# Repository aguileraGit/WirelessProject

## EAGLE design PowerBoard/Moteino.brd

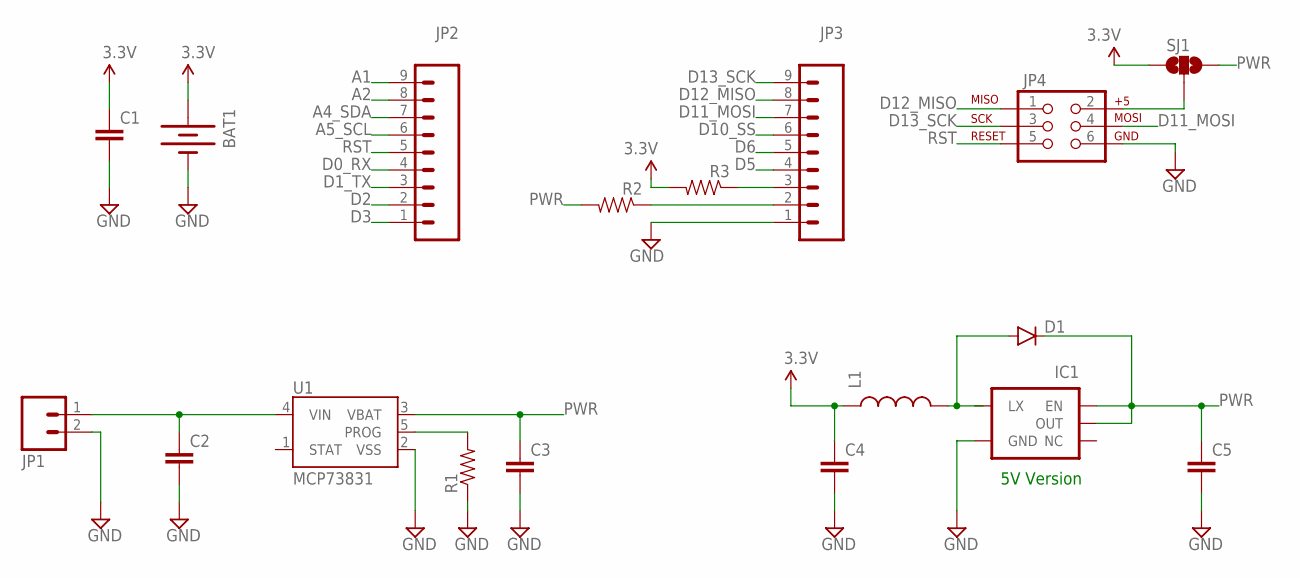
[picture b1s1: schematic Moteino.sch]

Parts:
BAT1: BATTERY12MM; BATTCON_12MM
C1, C2, C3, C4, C5: CAP0603-CAP; 0603-CAP
D1: DIODESMA; SMA-DIODE
IC1: V_REG_NCP1400SOT23-5; SOT23-5
JP1: M02PTH; 1X02
JP2, JP3: M09; 1X09
JP4: AVR_SPI_PRG_6TESTPOINTS; 2X3_TEST_POINTS
L1: INDUCTORINDUCTOR_4.7UH; INDUCTOR_4.7UH
R1, R2, R3: RESISTOR0603-RES; 0603-RES
SJ1: JUMPER-PAD-3-NOFULL_BOX_SILK; PAD-JUMPER-3-NO_YES_SILK_FULL_BOX
U1: MCP73831; SOT23-5

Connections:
A1: JP2.9
A2: JP2.8
A4_SDA: JP2.7
A5_SCL: JP2.6
D0_RX: JP2.4
D1_TX: JP2.3
D2: JP2.2
D3: JP2.1
D5: JP3.4
D6: JP3.5
D10_SS: JP3.6
D11_MOSI: JP3.7, JP4.4
D12_MISO: JP3.8, JP4.1
D13_SCK: JP3.9, JP4.3
GND: BAT1.GND (-), C1.2, C2.2, C3.2, C4.2, C5.2, IC1.4 (GND), JP1.2, JP3.1, JP4.6, R1.1, U1.2 (VSS)
unnamed: JP3.2, R2.1
unnamed: JP3.3, R3.1
unnamed: C2.1, JP1.1, U1.4 (VIN)
unnamed: R1.2, U1.5 (PROG)
unnamed: D1.A, L1.P$2 (2)
unnamed: JP4.2, SJ1.2
PWR: C3.1, C5.1, D1.C, IC1.1 (EN), IC1.2 (OUT), R2.2, SJ1.3, U1.3 (VBAT)
RST: JP2.5, JP4.5
VCC: BAT1.PWR@1 (+), C1.1, C4.1, L1.P$1 (1), R3.2, SJ1.1

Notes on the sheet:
5V Version

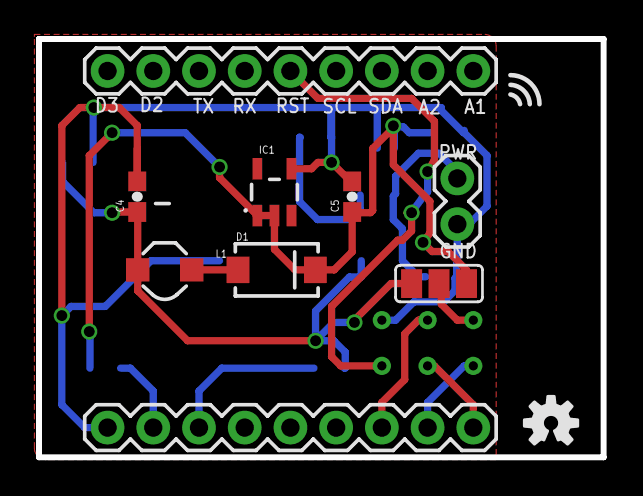
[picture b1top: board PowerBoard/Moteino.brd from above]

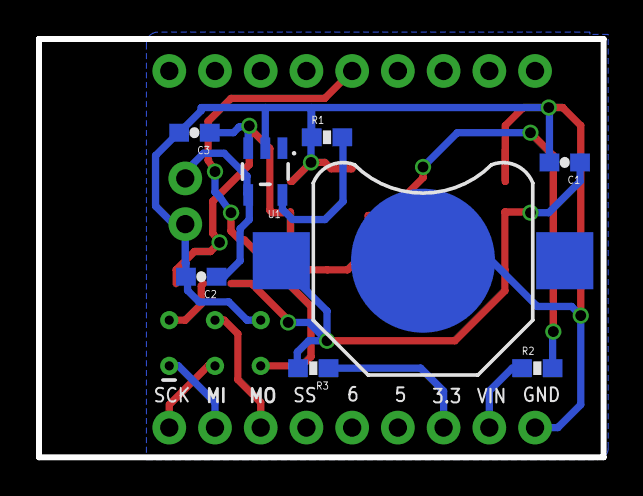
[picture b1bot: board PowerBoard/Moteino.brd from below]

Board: 2 copper layers, 31.4 x 23.2 mm, 19 parts (9 on the bottom side), 13 nets.

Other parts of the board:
U$3: OSHW-LOGO-S

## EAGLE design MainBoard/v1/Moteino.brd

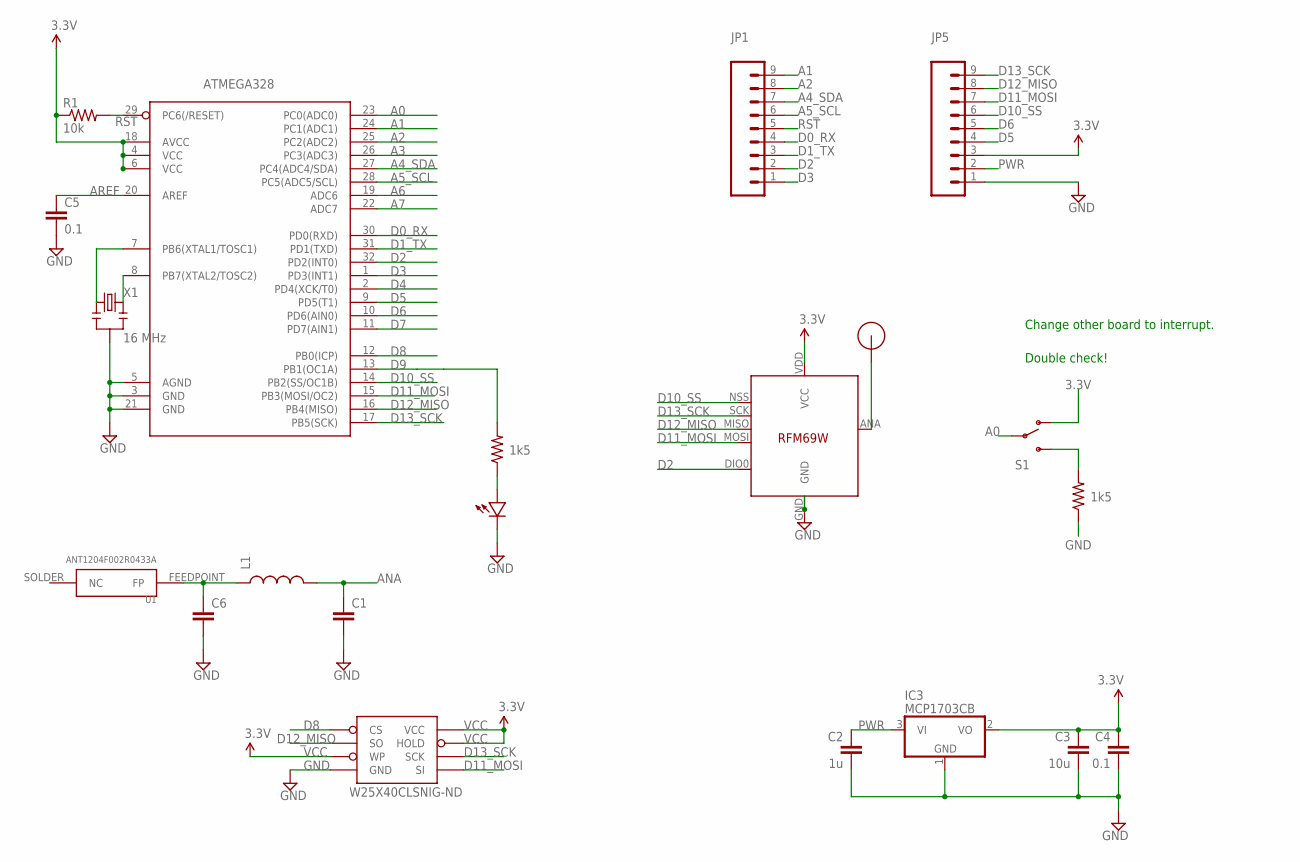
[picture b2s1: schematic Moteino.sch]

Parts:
ATMEGA328: ATMega-328; TQFP32-08
C1, C6: CAP0603-CAP; 0603-CAP
C2: 1u; 0603-CAP
C3: 10u; 0805-CAP
C4, C5: 0.1; 0603-CAP
IC3: MCP1703CB; SOT23
JP1, JP5: M09; 1X09
L1: INDUCTOR0603; 0603
R1: 10k; 0603-RES
R2, R3: 1k5; 0603-RES
S1: SWITCH-SPDT-SMD-A; SWITCH-SPST-SMD-A
U1: ANT1204F002R0433A
U$1: RFM12B_ANTENNA; RFM12B-ANTENNA
U$2: LED0603; 0603-LED
U$5: RFM69; RFM69W-MINPADS
W25X40CLSNIG-ND: AT25F512BWIDE_5.3MM; SO08WIDE
X1: 16 MHz; RESONATOR-SMD

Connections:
3.3V: S1.1 (O)
A0: ATMEGA328.23 (PC0(ADC0)), S1.2
A1: ATMEGA328.24 (PC1(ADC1)), JP1.9
A2: ATMEGA328.25 (PC2(ADC2)), JP1.8
A3: ATMEGA328.26 (PC3(ADC3))
A4_SDA: ATMEGA328.27 (PC4(ADC4/SDA)), JP1.7
A5_SCL: ATMEGA328.28 (PC5(ADC5/SCL)), JP1.6
A6: ATMEGA328.19 (ADC6)
A7: ATMEGA328.22 (ADC7)
ANA: C1.1, L1.2, U$1.P$1, U$5.ANA (ANT)
AREF: ATMEGA328.20 (AREF), C5.1
D0_RX: ATMEGA328.30 (PD0(RXD)), JP1.4
D1_TX: ATMEGA328.31 (PD1(TXD)), JP1.3
D2: ATMEGA328.32 (PD2(INT0)), JP1.2, U$5.DIO0
D3: ATMEGA328.1 (PD3(INT1)), JP1.1
D4: ATMEGA328.2 (PD4(XCK/T0))
D5: ATMEGA328.9 (PD5(T1)), JP5.4
D6: ATMEGA328.10 (PD6(AIN0)), JP5.5
D7: ATMEGA328.11 (PD7(AIN1))
D8: ATMEGA328.12 (PB0(ICP)), W25X40CLSNIG-ND.1 (CS)
D9: ATMEGA328.13 (PB1(OC1A)), R2.2
D10_SS: ATMEGA328.14 (PB2(SS/OC1B)), JP5.6, U$5.NSS (SEL)
D11_MOSI: ATMEGA328.15 (PB3(MOSI/OC2)), JP5.7, U$5.MOSI, W25X40CLSNIG-ND.5 (SI)
D12_MISO: ATMEGA328.16 (PB4(MISO)), JP5.8, U$5.MISO, W25X40CLSNIG-ND.2 (SO)
D13_SCK: ATMEGA328.17 (PB5(SCK)), JP5.9, U$5.SCK, W25X40CLSNIG-ND.6 (SCK)
GND: ATMEGA328.3 (GND), ATMEGA328.5 (AGND), ATMEGA328.21 (GND), C1.2, C2.2, C3.2, C4.2, C5.2, C6.2, IC3.1 (GND), JP5.1, R3.1, U$2.MINUS, U$5.GND, W25X40CLSNIG-ND.4 (GND), X1.2
unnamed: ATMEGA328.7 (PB6(XTAL1/TOSC1)), X1.1
unnamed: R2.1, U$2.PLUS
unnamed: R3.2, S1.3 (S)
unnamed: C6.1, L1.1, U1.FEEDPOINT (FP)
unnamed: ATMEGA328.8 (PB7(XTAL2/TOSC2)), X1.3
PWR: C2.1, IC3.3 (VI), JP5.2
RST: ATMEGA328.29 (PC6(/RESET)), JP1.5, R1.2
VCC: ATMEGA328.4 (VCC), ATMEGA328.6 (VCC), ATMEGA328.18 (AVCC), C3.1, C4.1, IC3.2 (VO), JP5.3, R1.1, U$5.VDD (VCC), W25X40CLSNIG-ND.3 (WP), W25X40CLSNIG-ND.7 (HOLD), W25X40CLSNIG-ND.8 (VCC)

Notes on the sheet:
Double check!
Change other board to interrupt.

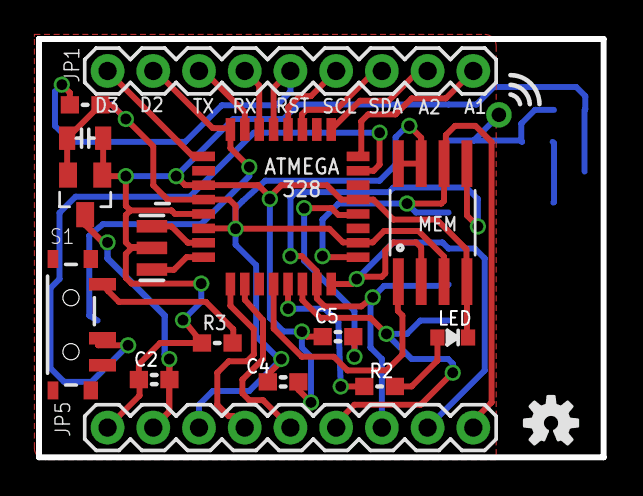
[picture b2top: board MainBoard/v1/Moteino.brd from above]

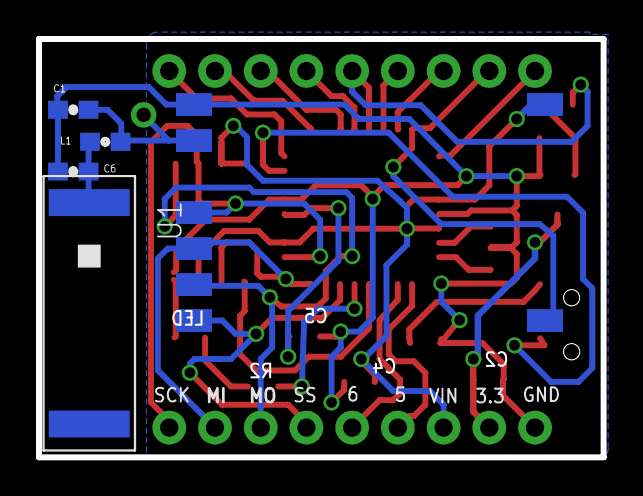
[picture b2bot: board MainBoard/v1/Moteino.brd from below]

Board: 2 copper layers, 31.4 x 23.2 mm, 22 parts (5 on the bottom side), 28 nets.

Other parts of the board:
U$3: OSHW-LOGO-S

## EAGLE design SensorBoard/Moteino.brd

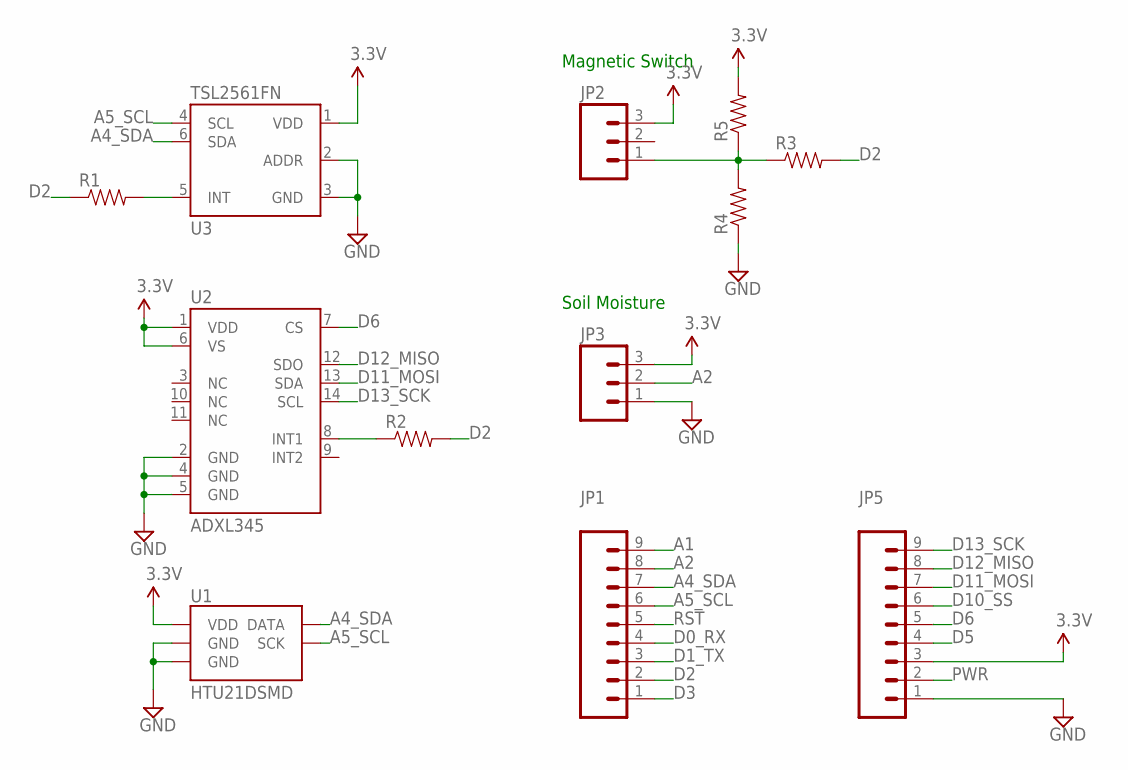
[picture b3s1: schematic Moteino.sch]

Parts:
JP1, JP5: M09; 1X09
JP2, JP3: M03PTH; 1X03
R1, R2, R3, R4, R5: RESISTOR0603-RES; 0603-RES
U1: HTU21DSMD; HTU21D
U2: ADXL345; LGA14
U3: TSL2561FN; FN-6

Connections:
A1: JP1.9
A2: JP1.8, JP3.2
A4_SDA: JP1.7, U1.DATA, U3.6 (SDA)
A5_SCL: JP1.6, U1.SCK, U3.4 (SCL)
D0_RX: JP1.4
D1_TX: JP1.3
D2: JP1.2, R1.1, R2.2, R3.2
D3: JP1.1
D5: JP5.4
D6: JP5.5, U2.7 (CS)
D10_SS: JP5.6
D11_MOSI: JP5.7, U2.13 (SDA)
D12_MISO: JP5.8, U2.12 (SDO)
D13_SCK: JP5.9, U2.14 (SCL)
GND: JP3.1, JP5.1, R4.1, U1.7 (GND), U1.GND, U2.2 (GND), U2.4 (GND), U2.5 (GND), U3.2 (ADDR), U3.3 (GND)
unnamed: JP2.1, R3.1, R4.2, R5.1
unnamed: R1.2, U3.5 (INT)
unnamed: R2.1, U2.8 (INT1)
PWR: JP5.2
RST: JP1.5
VCC: JP2.3, JP3.3, JP5.3, R5.2, U1.VDD, U2.1 (VDD), U2.6 (VS), U3.1 (VDD)

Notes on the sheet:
Magnetic Switch
Soil Moisture

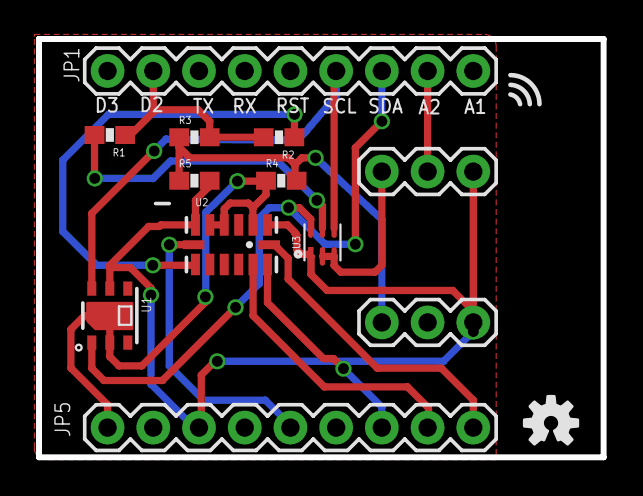
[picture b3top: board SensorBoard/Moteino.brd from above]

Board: 2 copper layers, 31.4 x 23.2 mm, 13 parts (0 on the bottom side), 13 nets.

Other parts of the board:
U$3: OSHW-LOGO-S

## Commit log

2015-07-31 Init Commit.
    Adding just the eagle files.

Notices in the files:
parts and their libraries:
SparkFun-Connectors: Licensing: CC v3.0 Share-Alike You are welcome to use this library for commercial purposes.
SparkFun-Electromechanical: Licensing: Creative Commons ShareAlike 4.0 International - https://creativecommons.org/licenses/by-sa/4.0
